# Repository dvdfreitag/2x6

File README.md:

# 2x6

Custom 2x6 mechanical keyboard with onboard controller

https://oshpark.com/shared_projects/wKzgsA9b

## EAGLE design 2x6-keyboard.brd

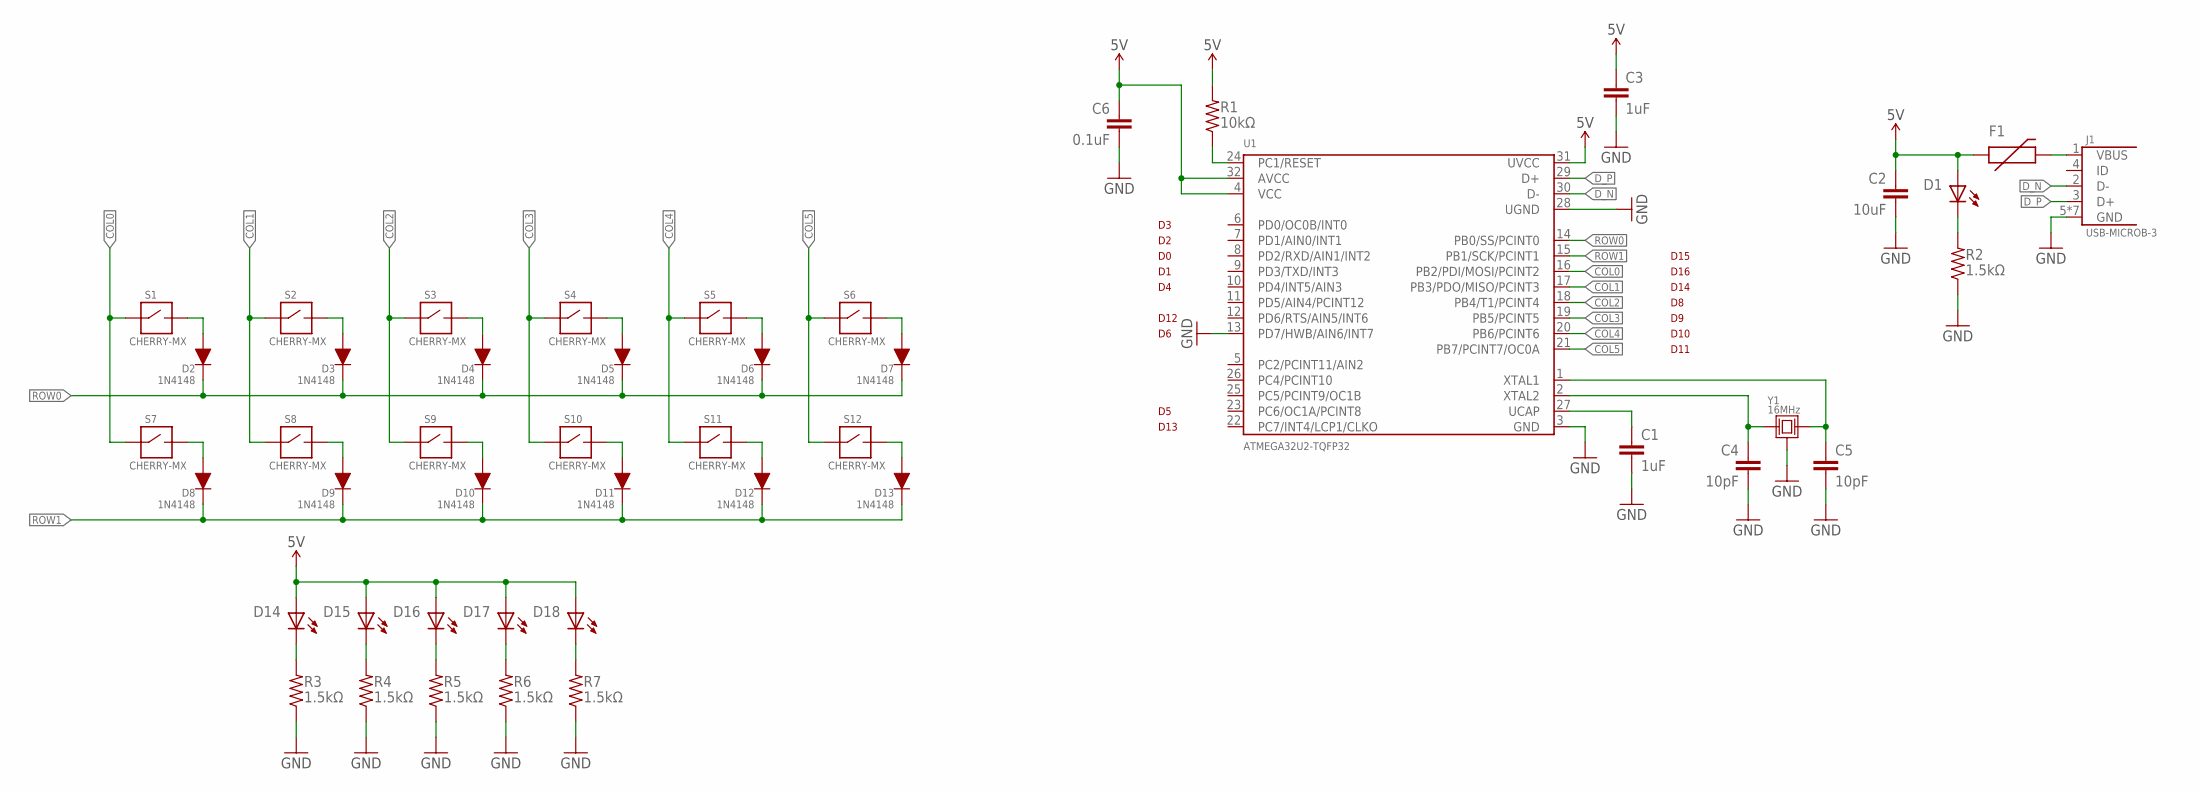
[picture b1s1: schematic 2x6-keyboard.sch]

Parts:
C1, C3: 1uF; 0603-CAP
C2: 10uF; 0603-CAP
C4, C5: 10pF; 0603-CAP
C6: 0.1uF; 0603-CAP
D1, D14, D15, D16, D17, D18: LED-0603; 0603-LED
D2, D3, D4, D5, D6, D7, D8, D9, D10, D11, D12, D13: 1N4148; SOD-123
F1: PTC-1206; 1206-PTC
J1: USB-MICROB-3; 10118192-0001LF
R1: 10kΩ; 0603-CAP
R2, R3, R4, R5, R6, R7: 1.5kΩ; 0603-CAP
S1, S2, S3, S4, S5, S6, S7, S8, S9, S10, S11, S12: CHERRY-MX
U1: ATMEGA32U2-TQFP32; TQFP-32
Y1: 16MHz; FA-238

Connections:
5V: C2.1, C3.1, C6.1, D1.A, D14.A, D15.A, D16.A, D17.A, D18.A, F1.P$1 (1), R1.2, U1.4 (VCC), U1.31 (UVCC), U1.32 (AVCC)
COL0: S1.S1, S1.S4 (S1), S7.S1, S7.S4 (S1), U1.16 (PB2/PDI/MOSI/PCINT2)
COL1: S2.S1, S2.S4 (S1), S8.S1, S8.S4 (S1), U1.17 (PB3/PDO/MISO/PCINT3)
COL2: S3.S1, S3.S4 (S1), S9.S1, S9.S4 (S1), U1.18 (PB4/T1/PCINT4)
COL3: S4.S1, S4.S4 (S1), S10.S1, S10.S4 (S1), U1.19 (PB5/PCINT5)
COL4: S5.S1, S5.S4 (S1), S11.S1, S11.S4 (S1), U1.20 (PB6/PCINT6)
COL5: S6.S1, S6.S4 (S1), S12.S1, S12.S4 (S1), U1.21 (PB7/PCINT7/OC0A)
D_N: J1.2 (D-), U1.30 (D-)
D_P: J1.3 (D+), U1.29 (D+)
GND: C1.2, C2.2, C3.2, C4.2, C5.2, C6.2, J1.5 (GND), J1.P$6 (GND), J1.P$7 (GND), J1.P$8 (GND), J1.P$9 (GND), J1.P$10 (GND), J1.P$11 (GND), R2.1, R3.1, R4.1, R5.1, R6.1, R7.1, U1.3 (GND), U1.13 (PD7/HWB/AIN6/INT7), U1.28 (UGND), Y1.2 (GND), Y1.4 (GND)
unnamed: C1.1, U1.27 (UCAP)
unnamed: D14.C, R3.2
unnamed: R1.1, U1.24 (PC1/RESET)
unnamed: F1.P$2 (2), J1.1 (VBUS)
unnamed: D1.C, R2.2
unnamed: C5.1, U1.1 (XTAL1), Y1.3 (2)
unnamed: C4.1, U1.2 (XTAL2), Y1.1
unnamed: D7.2 (A), S6.S2, S6.S3 (S2)
unnamed: D6.2 (A), S5.S2, S5.S3 (S2)
unnamed: D5.2 (A), S4.S2, S4.S3 (S2)
unnamed: D4.2 (A), S3.S2, S3.S3 (S2)
unnamed: D3.2 (A), S2.S2, S2.S3 (S2)
unnamed: D2.2 (A), S1.S2, S1.S3 (S2)
unnamed: D15.C, R4.2
unnamed: D8.2 (A), S7.S2, S7.S3 (S2)
unnamed: D9.2 (A), S8.S2, S8.S3 (S2)
unnamed: D10.2 (A), S9.S2, S9.S3 (S2)
unnamed: D11.2 (A), S10.S2, S10.S3 (S2)
unnamed: D12.2 (A), S11.S2, S11.S3 (S2)
unnamed: D13.2 (A), S12.S2, S12.S3 (S2)
unnamed: D16.C, R5.2
unnamed: D17.C, R6.2
unnamed: D18.C, R7.2
ROW0: D2.1 (C), D3.1 (C), D4.1 (C), D5.1 (C), D6.1 (C), D7.1 (C), U1.14 (PB0/SS/PCINT0)
ROW1: D8.1 (C), D9.1 (C), D10.1 (C), D11.1 (C), D12.1 (C), D13.1 (C), U1.15 (PB1/SCK/PCINT1)

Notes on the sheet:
D10
D11
D12
D13
D14
D15
D16

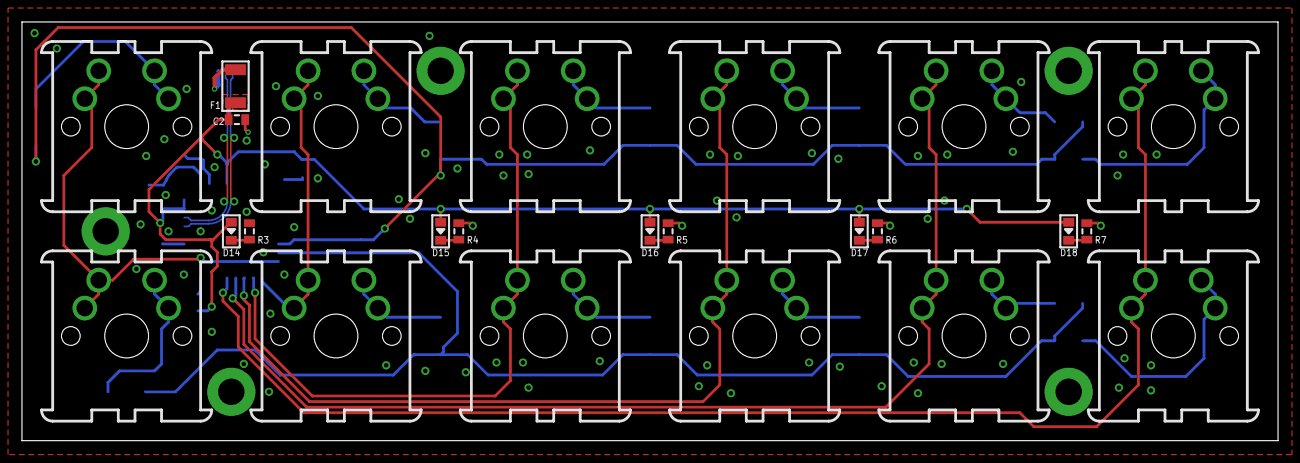
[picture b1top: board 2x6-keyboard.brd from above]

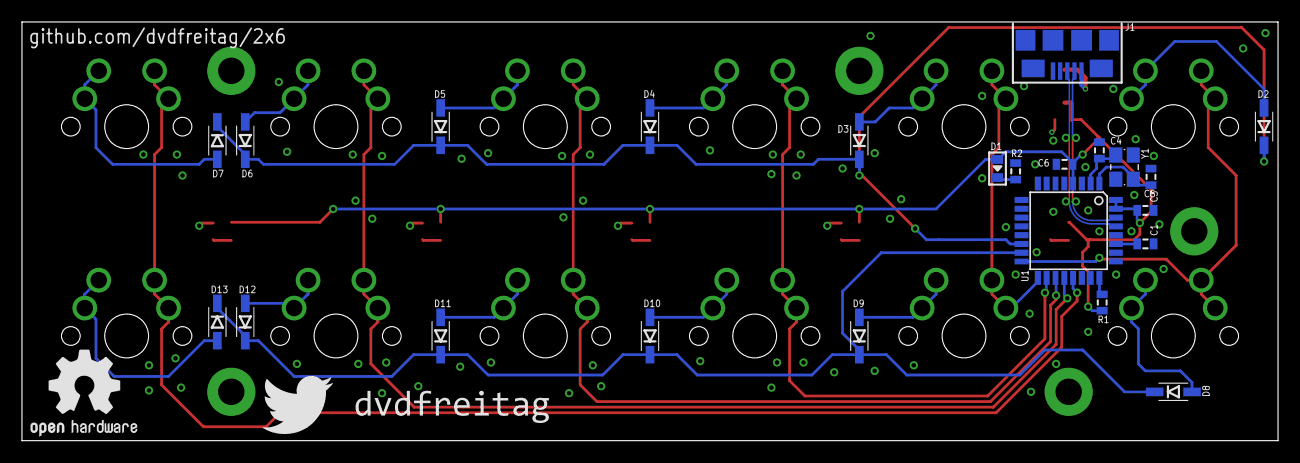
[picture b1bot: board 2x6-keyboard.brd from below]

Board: 2 copper layers, 114.3 x 38.1 mm, 49 parts (25 on the bottom side), 35 nets.

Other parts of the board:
U$1: OSHW
U$2: TWITTER
